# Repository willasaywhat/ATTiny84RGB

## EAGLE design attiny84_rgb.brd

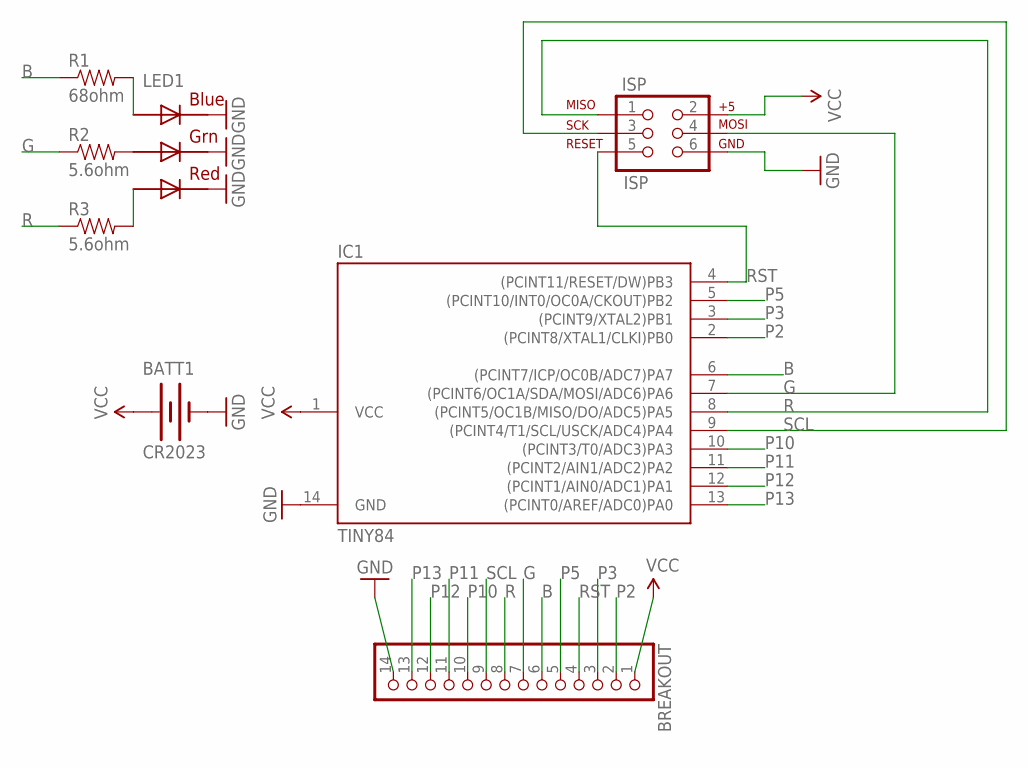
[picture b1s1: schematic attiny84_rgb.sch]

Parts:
BATT1: CR2023; BATTCON_12MM
BREAKOUT: PINHD-1X14; 1X14
IC1: TINY84; SOIC14
ISP: ISP; 2X3-NS
LED1: LED1; RGBLED5050
R1: 68ohm; 1206
R2, R3: 5.6ohm; 1206

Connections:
B: BREAKOUT.6, IC1.6 ((PCINT7/ICP/OC0B/ADC7)PA7), R1.1
G: BREAKOUT.7, IC1.7 ((PCINT6/OC1A/SDA/MOSI/ADC6)PA6), ISP.4, R2.1
GND: BATT1.GND (-), BREAKOUT.14, IC1.14 (GND), ISP.6, LED1.4 (BLUE_C), LED1.5 (RED_C), LED1.6 (GREEN_C)
unnamed: LED1.3 (BLUE_A), R1.2
unnamed: LED1.1 (GREEN_A), R2.2
unnamed: LED1.2 (RED_A), R3.2
P2: BREAKOUT.2, IC1.2 ((PCINT8/XTAL1/CLKI)PB0)
P3: BREAKOUT.3, IC1.3 ((PCINT9/XTAL2)PB1)
P5: BREAKOUT.5, IC1.5 ((PCINT10/INT0/OC0A/CKOUT)PB2)
P10: BREAKOUT.10, IC1.10 ((PCINT3/T0/ADC3)PA3)
P11: BREAKOUT.11, IC1.11 ((PCINT2/AIN1/ADC2)PA2)
P12: BREAKOUT.12, IC1.12 ((PCINT1/AIN0/ADC1)PA1)
P13: BREAKOUT.13, IC1.13 ((PCINT0/AREF/ADC0)PA0)
R: BREAKOUT.8, IC1.8 ((PCINT5/OC1B/MISO/DO/ADC5)PA5), ISP.1, R3.1
RST: BREAKOUT.4, IC1.4 ((PCINT11/RESET/DW)PB3), ISP.5
SCL: BREAKOUT.9, IC1.9 ((PCINT4/T1/SCL/USCK/ADC4)PA4), ISP.3
VCC: BATT1.PWR@1 (+), BREAKOUT.1, IC1.1 (VCC), ISP.2

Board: 2 copper layers, 8 parts (1 on the bottom side), 17 nets, no tracks yet.

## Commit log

2012-01-15 Added initial files

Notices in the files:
parts and their libraries:
SparkFun: Licensing: CC v3.0 Share-Alike You are welcome to use this library for commercial purposes.
